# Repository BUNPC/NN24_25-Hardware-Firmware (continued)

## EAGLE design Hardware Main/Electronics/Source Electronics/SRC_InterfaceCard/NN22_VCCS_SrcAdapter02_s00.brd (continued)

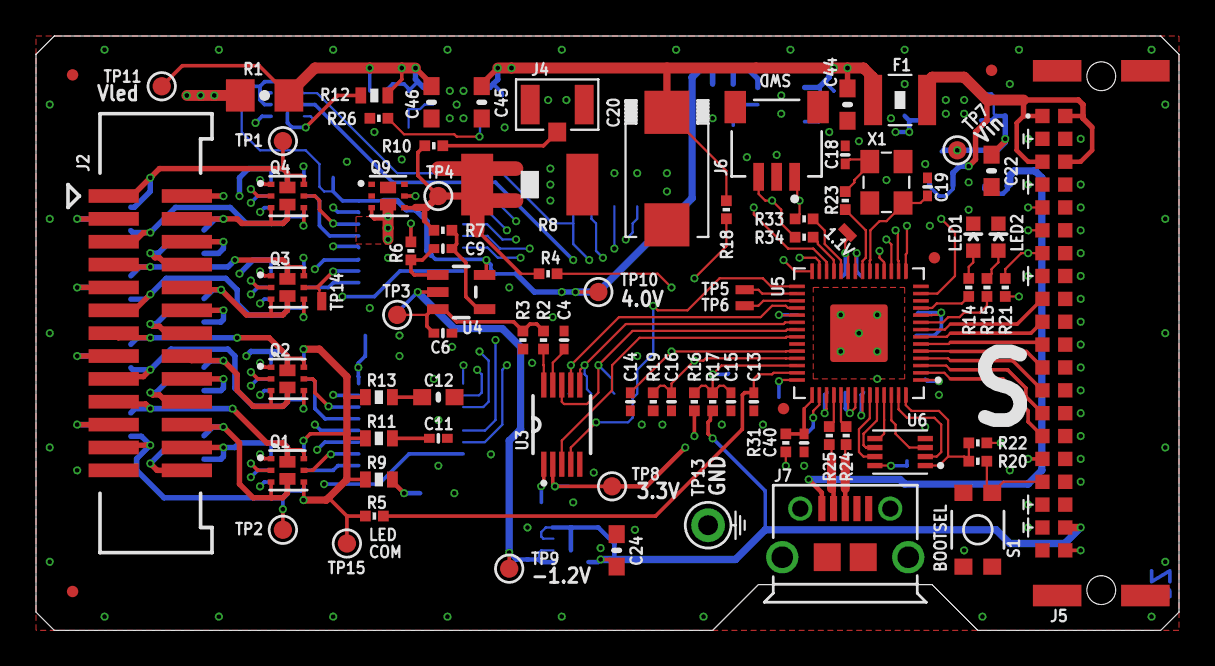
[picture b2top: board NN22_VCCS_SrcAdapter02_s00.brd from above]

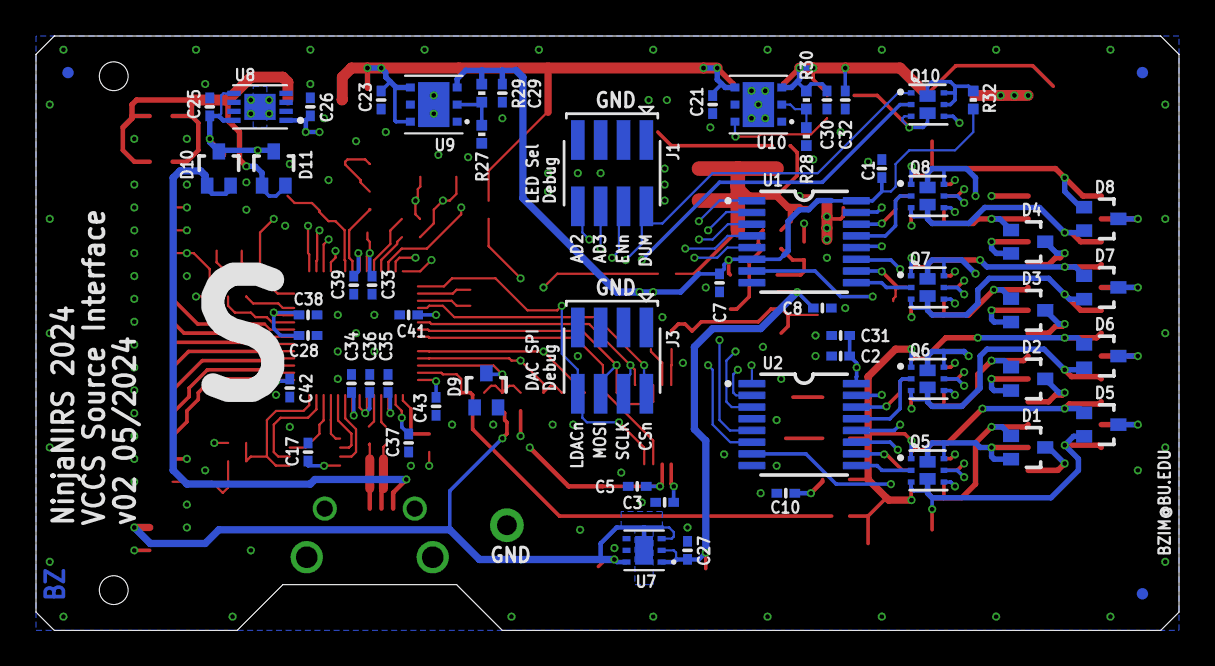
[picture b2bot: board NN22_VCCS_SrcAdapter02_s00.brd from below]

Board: 4 copper layers, 63.5 x 33.0 mm, 146 parts (60 on the bottom side), 109 nets.

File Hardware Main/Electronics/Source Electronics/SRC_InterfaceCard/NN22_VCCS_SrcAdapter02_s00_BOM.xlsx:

Designator | Value | Footprint | Populate | MPN | Manufacturer | MPN | Manufacturer
C1 | 0.1u | 0402-CAP | 1 | GRM155R71H104KE14D | Murata
C10 | 0.1u | 0402-CAP | 1 | GRM155R71H104KE14D | Murata
C11 | 10n | 0402-CAP | 1 | CL05B103KB5NNNC | Samsung
C12 | DNP | 0603-CAP | 0
C13 | 100p | 0402-CAP | 1 | CL05C101JB5NNNC | Samsung
C14 | 100p | 0402-CAP | 1 | CL05C101JB5NNNC | Samsung
C15 | 100p | 0402-CAP | 1 | CL05C101JB5NNNC | Samsung
C16 | 100p | 0402-CAP | 1 | CL05C101JB5NNNC | Samsung
C17 | 0.1u | 0402-CAP | 1 | GRM155R71H104KE14D | Murata
C18 | 27p | 0402-CAP | 1 | GCM1555C1H270JA16D | Murata
C19 | 27p | 0402-CAP | 1 | GCM1555C1H270JA16D | Murata
C2 | 0.1u | 0402-CAP | 1 | GRM155R71H104KE14D | Murata
C20 | 150u | 2917-CAP | 1 | TCJY157M016R0050E | KYOCERA AVX
C21 | 0.1u | 0402-CAP | 1 | GRM155R71H104KE14D | Murata
C22 | 10u | 0603-CAP | 1 | GRM188R6YA106MA73D | Murata
C23 | 0.1u | 0402-CAP | 1 | GRM155R71H104KE14D | Murata
C24 | 10u | 0603-CAP | 1 | GRM188R6YA106MA73D | Murata
C25 | 0.1u | 0402-CAP | 1 | GRM155R71H104KE14D | Murata
C26 | 4.7u | 0402-CAP | 1 | CL05A475MP5NRNC | Samsung
C27 | 4.7u | 0402-CAP | 1 | CL05A475MP5NRNC | Samsung
C28 | 4.7u | 0402-CAP | 1 | CL05A475MP5NRNC | Samsung
C29 | 4.7u | 0402-CAP | 1 | CL05A475MP5NRNC | Samsung
C3 | 0.1u | 0402-CAP | 1 | GRM155R71H104KE14D | Murata
C30 | 0.1u | 0402-CAP | 1 | GRM155R71H104KE14D | Murata
C31 | 4.7u | 0402-CAP | 1 | CL05A475MP5NRNC | Samsung
C32 | DNP | 0402-CAP | 0
C33 | 0.1u | 0402-CAP | 1 | GRM155R71H104KE14D | Murata
C34 | 0.1u | 0402-CAP | 1 | GRM155R71H104KE14D | Murata
C35 | 4.7u | 0402-CAP | 1 | CL05A475MP5NRNC | Samsung
C36 | 0.1u | 0402-CAP | 1 | GRM155R71H104KE14D | Murata
C37 | 4.7u | 0402-CAP | 1 | CL05A475MP5NRNC | Samsung
C38 | 0.1u | 0402-CAP | 1 | GRM155R71H104KE14D | Murata
C39 | 0.1u | 0402-CAP | 1 | GRM155R71H104KE14D | Murata
C4 | 10n | 0402-CAP | 1 | CL05B103KB5NNNC | Samsung
C40 | 4.7u | 0402-CAP | 1 | CL05A475MP5NRNC | Samsung
C41 | 0.1u | 0402-CAP | 1 | GRM155R71H104KE14D | Murata
C42 | 0.1u | 0402-CAP | 1 | GRM155R71H104KE14D | Murata
C43 | 0.1u | 0402-CAP | 1 | GRM155R71H104KE14D | Murata
C44 | 10u | 0603-CAP | 1 | GRM188R6YA106MA73D | Murata
C45 | 10u | 0603-CAP | 1 | GRM188R6YA106MA73D | Murata
C46 | 10u | 0603-CAP | 1 | GRM188R6YA106MA73D | Murata
C5 | 0.1u | 0402-CAP | 1 | GRM155R71H104KE14D | Murata
C6 | 100p | 0402-CAP | 1 | CL05C101JB5NNNC | Samsung
C7 | 0.1u | 0402-CAP | 1 | GRM155R71H104KE14D | Murata
C8 | 0.1u | 0402-CAP | 1 | GRM155R71H104KE14D | Murata
C9 | 100p | 0402-CAP | 1 | CL05C101JB5NNNC | Samsung
D1 | BAV70W | SOT323 | 1 | BAV70WT1G | onsemi
D10 | BAV70W | SOT323 | 1 | BAV70WT1G | onsemi
D11 | BAV70W | SOT323 | 1 | BAV70WT1G | onsemi
D2 | BAV70W | SOT323 | 1 | BAV70WT1G | onsemi
D3 | BAV70W | SOT323 | 1 | BAV70WT1G | onsemi
D4 | BAV70W | SOT323 | 1 | BAV70WT1G | onsemi
D5 | BAV70W | SOT323 | 1 | BAV70WT1G | onsemi
D6 | BAV70W | SOT323 | 1 | BAV70WT1G | onsemi
D7 | BAV70W | SOT323 | 1 | BAV70WT1G | onsemi
D8 | BAV70W | SOT323 | 1 | BAV70WT1G | onsemi
D9 | BAV70W | SOT323 | 1 | BAV70WT1G | onsemi
F1 | 0ZCH0035FF2G | 1210-FUSE | 1 | 0ZCH0035FF2G | Bel Fuse
FID1 | FIDUCIALUFIDUCIAL | MICRO-FIDUCIAL | 0
FID2 | FIDUCIALUFIDUCIAL | MICRO-FIDUCIAL | 0
FID3 | FIDUCIALUFIDUCIAL | MICRO-FIDUCIAL | 0
FID4 | FIDUCIALUFIDUCIAL | MICRO-FIDUCIAL | 0
FID5 | FIDUCIALUFIDUCIAL | MICRO-FIDUCIAL | 0
FID6 | FIDUCIALUFIDUCIAL | MICRO-FIDUCIAL | 0
FID7 | FIDUCIALUFIDUCIAL | MICRO-FIDUCIAL | 0
FID8 | FIDUCIALUFIDUCIAL | MICRO-FIDUCIAL | 0
J1 | M04X2_0.050_SMD_NO_CREAM | M04X2_0.050_SMD_NO_CREAM | 0
J2 | M13X2_0.050_SHF | M13X2_0.050_SHF | 1 | 3220-26-0300-00 | CNC Tech | 3220-26-0300-00-TR | CNC Tech
J3 | M04X2_0.050_SMD_NO_CREAM | M04X2_0.050_SMD_NO_CREAM | 0
J4 | U.FL | U.FL | 1 | 1909763-1 | TE Connectivity
J5 | M20X2_HARFLEX_M | M20X2_HARFLEX_M | 1 | 15150402601000 | HARTING Elektronik
J6 | M03X1_JST_SH_RA | M03X1_JST_SH_SM_RA | 1 | SM03B-SRSS-TB | JST
J7 | USB-MICRO | USB-MICRO | 1 | 10118194-0001LF | Amphenol Communications Solutions
LED1 |  | LED-0603 | 1 | LTST-C191KRKT | Lite-On
LED2 |  | LED-0603 | 1 | LTST-C191KGKT | Lite-On
Q1 | MOSFET-DUAL-N-UDFN8 | UDFN8 | 1 | SSM6N67NU,LF | Toshiba
Q10 | MOSFET-DUAL-N-UDFN8 | UDFN8 | 1 | SSM6N67NU,LF | Toshiba
Q2 | MOSFET-DUAL-N-UDFN8 | UDFN8 | 1 | SSM6N67NU,LF | Toshiba
Q3 | MOSFET-DUAL-N-UDFN8 | UDFN8 | 1 | SSM6N67NU,LF | Toshiba
Q4 | MOSFET-DUAL-N-UDFN8 | UDFN8 | 1 | SSM6N67NU,LF | Toshiba
Q5 | MOSFET-DUAL-N-UDFN8 | UDFN8 | 1 | SSM6N67NU,LF | Toshiba
Q6 | MOSFET-DUAL-N-UDFN8 | UDFN8 | 1 | SSM6N67NU,LF | Toshiba
Q7 | MOSFET-DUAL-N-UDFN8 | UDFN8 | 1 | SSM6N67NU,LF | Toshiba
Q8 | MOSFET-DUAL-N-UDFN8 | UDFN8 | 1 | SSM6N67NU,LF | Toshiba
Q9 | MOSFET-DUAL-N-UDFN8 | UDFN8 | 1 | SSM6N67NU,LF | Toshiba
R1 | 0 | 1206 | 1 | RC1206JR-070RL | Yageo
R10 | 100 | 0402-RES | 1 | RC0402FR-07100RL | Yageo
R11 | 1 | 0603-RES | 1 | RC0603FR-071RL | Yageo
R12 | 150 | 0603-RES | 1 | RC0603FR-07150RL | Yageo
R13 | DNP | 0603-RES | 0
R14 | 1.2k | 0402-RES | 1 | RC0402FR-071K2L | Yageo
R15 | 1.2k | 0402-RES | 1 | RC0402FR-071K2L | Yageo
R16 | 10k | 0402-RES | 1 | RC0402FR-1310KL | Yageo
R17 | 28k | 0402-RES | 1 | RC0402FR-0728KL | Yageo
R18 | 28k | 0402-RES | 1 | RC0402FR-0728KL | Yageo
R19 | 10k | 0402-RES | 1 | RC0402FR-1310KL | Yageo
R2 | 10k | 0402-RES | 1 | RC0402FR-1310KL | Yageo
R20 | 1.2k | 0402-RES | 1 | RC0402FR-071K2L | Yageo
R21 | 100k | 0402-RES | 1 | RC0402FR-07100KL | Yageo
R22 | 100k | 0402-RES | 1 | RC0402FR-07100KL | Yageo
R23 | 1.2k | 0402-RES | 1 | RC0402FR-071K2L | Yageo
R24 | 27 | 0402-RES | 1 | RC0402FR-0727RL | Yageo
R25 | 27 | 0402-RES | 1 | RC0402FR-0727RL | Yageo
R26 | 100k | 0402-RES | 1 | RC0402FR-07100KL | Yageo
R27 | 10k | 0402-RES | 1 | RC0402FR-1310KL | Yageo
R28 | 10k | 0402-RES | 1 | RC0402FR-1310KL | Yageo
R29 | 24k | 0402-RES | 1 | RC0402FR-0724KL | Yageo
R3 | 24k | 0402-RES | 1 | RC0402FR-0724KL | Yageo
R30 | 28k | 0402-RES | 1 | RC0402FR-0728KL | Yageo
R31 | 27 | 0402-RES | 1 | RC0402FR-0727RL | Yageo
R32 | 10k | 0402-RES | 1 | RC0402FR-1310KL | Yageo
R33 | 27 | 0402-RES | 1 | RC0402FR-0727RL | Yageo
R34 | 27 | 0402-RES | 1 | RC0402FR-0727RL | Yageo
R4 | 10k | 0402-RES | 1 | RC0402FR-1310KL | Yageo
R5 | 10k | 0402-RES | 1 | RC0402FR-1310KL | Yageo
R6 | 100 | 0402-RES | 1 | RC0402FR-07100RL | Yageo
R7 | 1.2k | 0402-RES | 1 | RC0402FR-071K2L | Yageo
R8 | 8.2 | R2512 | 1 | ERJ1TRQJ8R2U | Panasonic
R9 | 10 | 0603-RES | 1 | RC0603FR-0710RL | Yageo
S1 | SWITCH-MOMENTARY-2SMD-3 | TACTILE_SWITCH_SMD-3 | 1 | KMR231NGLFS | C&K Components
TP1 | TESTPOINT_ROUND | TESTPAD_ROUND | 0
TP10 | TESTPOINT_ROUND | TESTPAD_ROUND | 0
TP11 | TESTPOINT_ROUND | TESTPAD_ROUND | 0
TP12 | TESTPOINTPADSMALL | TESTPAD_SMALL | 0
TP13 | TESTPOINT1X01 | 1X01 | 0
TP14 | TESTPOINTPADSMALL | TESTPAD_SMALL | 0
TP15 | TESTPOINT_ROUND | TESTPAD_ROUND | 0
TP2 | TESTPOINT_ROUND | TESTPAD_ROUND | 0
TP3 | TESTPOINT_ROUND | TESTPAD_ROUND | 0
TP4 | TESTPOINT_ROUND | TESTPAD_ROUND | 0
TP5 | TESTPOINTPADSMALL | TESTPAD_SMALL | 0
TP6 | TESTPOINTPADSMALL | TESTPAD_SMALL | 0
TP7 | TESTPOINT_ROUND | TESTPAD_ROUND | 0
TP8 | TESTPOINT_ROUND | TESTPAD_ROUND | 0
TP9 | TESTPOINT_ROUND | TESTPAD_ROUND | 0
U1 | 74HC238_TSSOP | TSSOP16 | 1 | SN74HCS238PWR | Texas Instruments
U10 | LDL212_DFN6_3X3 | DFN6_3X3MM | 1 | LDL212PUR | STMicroelectronics
U2 | 74HC238_TSSOP | TSSOP16 | 1 | SN74HCS238PWR | Texas Instruments
U3 | AD5683R_MSOP | MSOP10 | 1 | AD5683RARMZ | Analog Devices
U4 | OPA392_SOT23 | SOT23-5 | 1 | OPA392DBVR | Texas Instruments
U5 | RP2040 | QFN-56_EP | 1 | SC0914(7) | Raspberry Pi
U6 | W25Q_USON | USON8L-2X3MM | 1 | W25Q16JVUXIQ TR | Winbond
U7 | ADP7182_WSON | WSON6 | 1 | ADP7182ACPZN-R7 | Analog Devices
U8 | MCP1755_DFN | DFN8_2X3MM | 1 | MCP1755-3302E/MC | Microchip
U9 | LDL212_DFN6_3X3 | DFN6_3X3MM | 1 | LDL212PUR | STMicroelectronics
X1 | CRYSTAL-3.2-2.5 | CRYSTAL-3.2-2.5 | 1 | 403I35D12M00000 | CTS Components

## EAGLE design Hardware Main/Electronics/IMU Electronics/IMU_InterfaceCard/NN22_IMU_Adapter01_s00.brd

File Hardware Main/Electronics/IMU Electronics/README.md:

# IMU Electronics

All IMU electronics files are located in this folder. 

There is not a dedicated IMU backboard part as the IMU interface cards are intended to be used with the existing detector backplanes in place of a detector interface card.

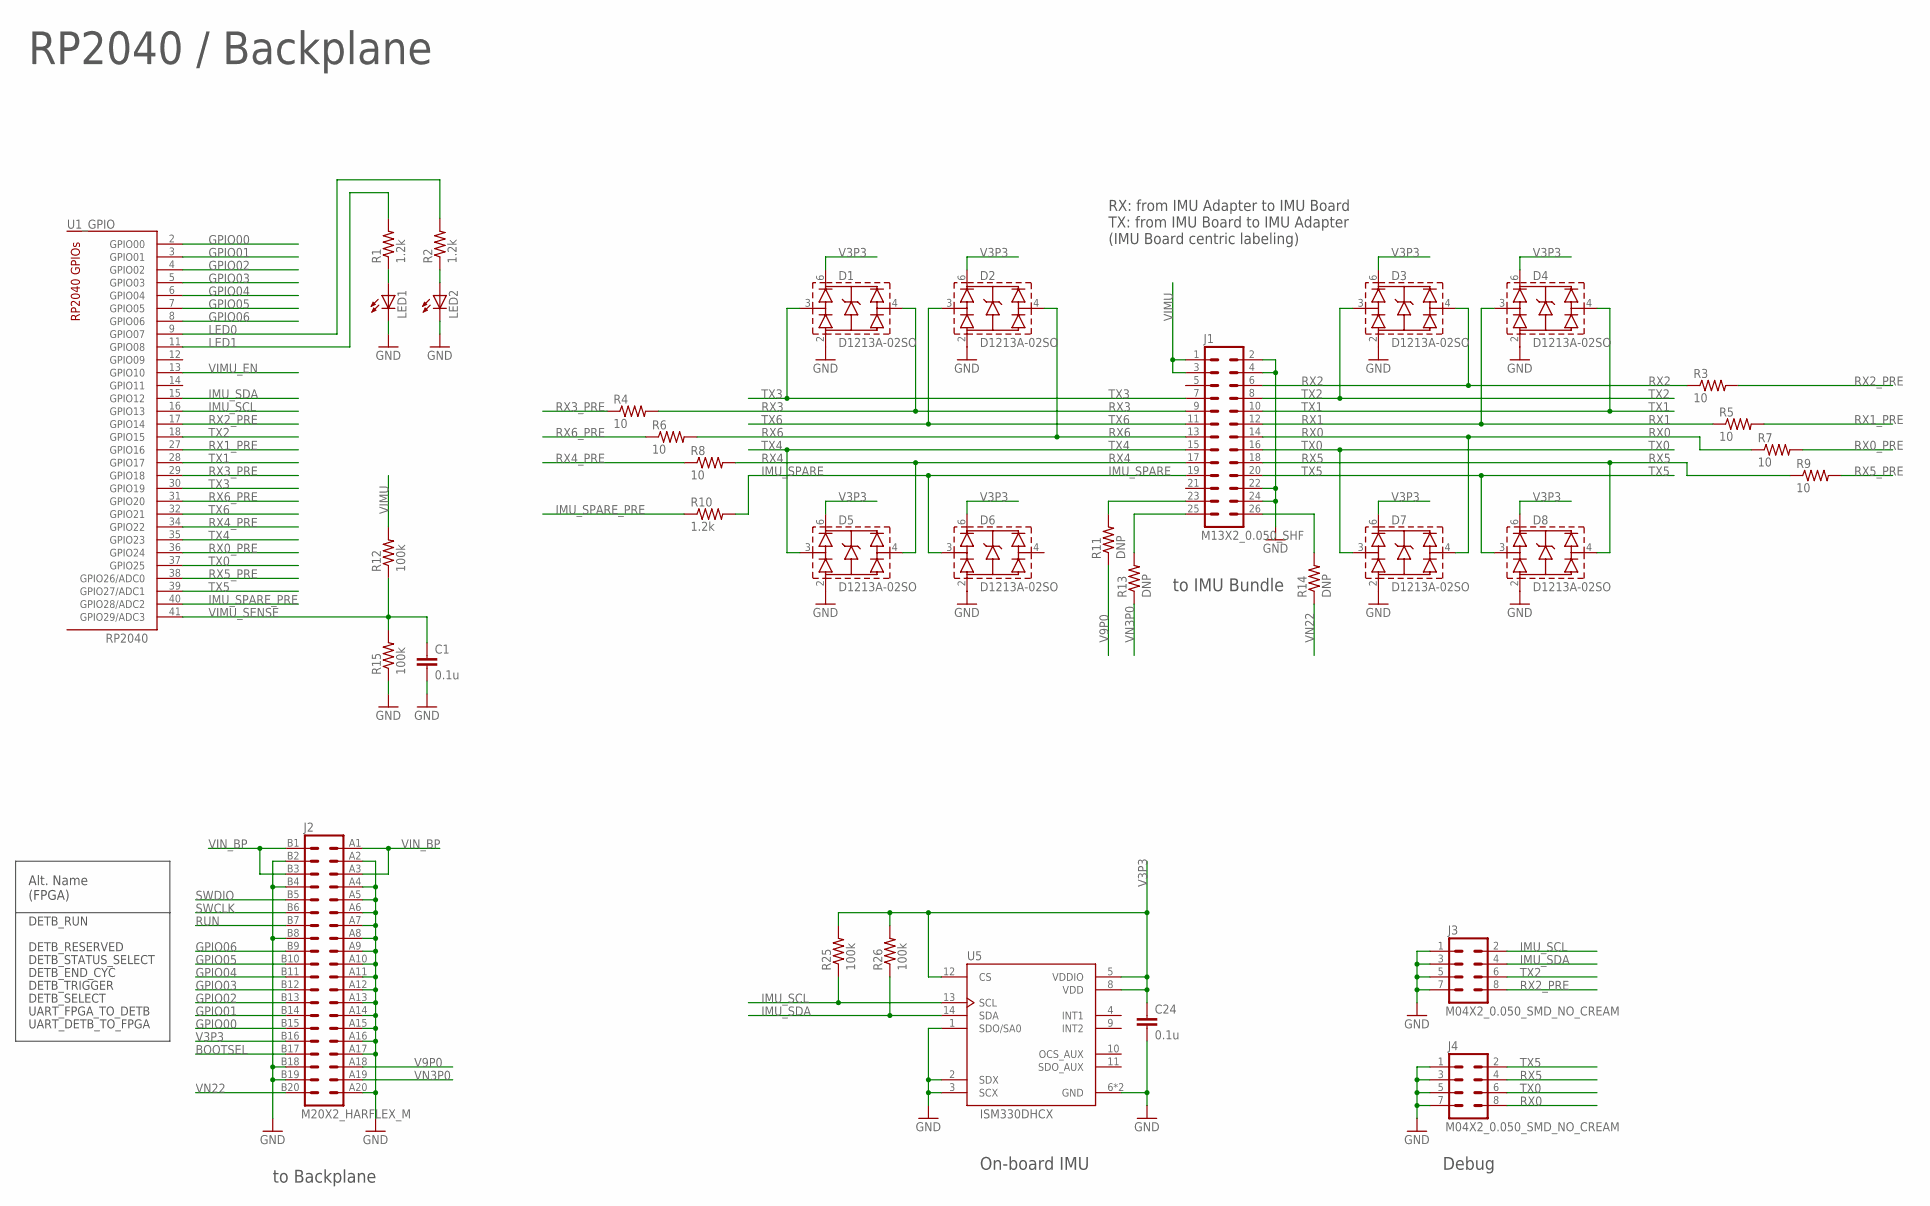
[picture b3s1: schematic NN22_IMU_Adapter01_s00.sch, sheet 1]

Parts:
C1, C24: 0.1u; 0402-CAP
D1, D2, D3, D4, D5, D6, D7, D8: D1213A-02SO; SOT23-6
J1: M13X2_0.050_SHF
J2: M20X2_HARFLEX_M
J3, J4: M04X2_0.050_SMD_NO_CREAM
LED1, LED2: LED0603; LED-0603
R1, R2, R10: 1.2k; 0402-RES
R3, R4, R5, R6, R7, R8, R9: 10; 0402-RES
R11, R13, R14: DNP; 0603-RES
R12, R15, R25, R26: 100k; 0402-RES
U1: RP2040; QFN-56_EP
U5: ISM330DHCX; LGA14-L

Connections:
BOOTSEL: J2.B17 (33); also elsewhere on the board
GND: C1.2, C24.2, D1.2 (VN), D2.2 (VN), D3.2 (VN), D4.2 (VN), D5.2 (VN), D6.2 (VN), D7.2 (VN), D8.2 (VN), J1.2, J1.4, J1.22, J1.24, J2.A2 (4), J2.A4 (8), J2.A5 (10), J2.A6 (12), J2.A7 (14), J2.A8 (16), J2.A9 (18), J2.A10 (20), J2.A11 (22), J2.A12 (24), J2.A13 (26), J2.A14 (28), J2.A15 (30), J2.A16 (32), J2.A17 (34), J2.A20 (40), J2.B2 (3), J2.B4 (7), J2.B8 (15), J2.B18 (35), J2.B19 (37), J3.1, J3.3, J3.5, J3.7, J4.1, J4.3, J4.5, J4.7, LED1.C, LED2.C, R15.1, U5.1 (SDO/SA0), U5.2 (SDX), U5.3 (SCX), U5.6 (GND), U5.7 (GND); also elsewhere on the board
GPIO00: J2.B15 (29), U1.2 (GPIO00)
GPIO01: J2.B14 (27), U1.3 (GPIO01)
GPIO02: J2.B13 (25), U1.4 (GPIO02)
GPIO03: J2.B12 (23), U1.5 (GPIO03)
GPIO04: J2.B11 (21), U1.6 (GPIO04)
GPIO05: J2.B10 (19), U1.7 (GPIO05)
GPIO06: J2.B9 (17), U1.8 (GPIO06)
IMU_SCL: J3.2, R25.1, U1.16 (GPIO13), U5.13 (SCL)
IMU_SDA: J3.4, R26.1, U1.15 (GPIO12), U5.14 (SDA)
IMU_SPARE: D6.3 (CH1), J1.19, R10.2
IMU_SPARE_PRE: R10.1, U1.40 (GPIO28/ADC2)
LED0: R2.2, U1.9 (GPIO07)
LED1: R1.2, U1.11 (GPIO08)
unnamed: J1.23, R11.2
unnamed: J1.25, R13.2
unnamed: J1.26, R14.2
unnamed: LED1.A, R1.1
unnamed: LED2.A, R2.1
RUN: J2.B7 (13); also elsewhere on the board
RX0: D7.4 (CH2), J1.14, J4.8, R7.1
RX0_PRE: R7.2, U1.36 (GPIO24)
RX1: D4.3 (CH1), J1.12, R5.1
RX1_PRE: R5.2, U1.27 (GPIO16)
RX2: D3.4 (CH2), J1.6, R3.1
RX2_PRE: J3.8, R3.2, U1.17 (GPIO14)
RX3: D1.4 (CH2), J1.9, R4.2
RX3_PRE: R4.1, U1.29 (GPIO18)
RX4: D5.4 (CH2), J1.17, R8.2
RX4_PRE: R8.1, U1.34 (GPIO22)
RX5: D8.4 (CH2), J1.18, J4.4, R9.1
RX5_PRE: R9.2, U1.38 (GPIO26/ADC0)
RX6: D2.4 (CH2), J1.13, R6.2
RX6_PRE: R6.1, U1.31 (GPIO20)
SWCLK: J2.B6 (11); also elsewhere on the board
SWDIO: J2.B5 (9); also elsewhere on the board
TX0: D7.3 (CH1), J1.16, J4.6, U1.37 (GPIO25)
TX1: D4.4 (CH2), J1.10, U1.28 (GPIO17)
TX2: D3.3 (CH1), J1.8, J3.6, U1.18 (GPIO15)
TX3: D1.3 (CH1), J1.7, U1.30 (GPIO19)
TX4: D5.3 (CH1), J1.15, U1.35 (GPIO23)
TX5: D8.3 (CH1), J1.20, J4.2, U1.39 (GPIO27/ADC1)
TX6: D2.3 (CH1), J1.11, U1.32 (GPIO21)
V3P3: C24.1, D1.6 (VP), D2.6 (VP), D3.6 (VP), D4.6 (VP), D5.6 (VP), D6.6 (VP), D7.6 (VP), D8.6 (VP), J2.B16 (31), R25.2, R26.2, U5.5 (VDDIO), U5.8 (VDD), U5.12 (CS); also elsewhere on the board
V9P0: J2.A18 (36), R11.1
VIMU: J1.1, J1.3, R12.2; also elsewhere on the board
VIMU_EN: U1.13 (GPIO10); also elsewhere on the board
VIMU_SENSE: C1.1, R12.1, R15.2, U1.41 (GPIO29/ADC3)
VIN_BP: J2.A1 (2), J2.A3 (6), J2.B1 (1), J2.B3 (5); also elsewhere on the board
VN3P0: J2.A19 (38), R13.1
VN22: J2.B20 (39), R14.1

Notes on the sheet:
RP2040 / Backplane
to Backplane
UART_DETB_TO_FPGA
UART_FPGA_TO_DETB
DETB_SELECT
DETB_TRIGGER
DETB_END_CYC
DETB_STATUS_SELECT
DETB_RESERVED
DETB_RUN
Alt. Name (FPGA)
to IMU Bundle
Debug
RX: from IMU Adapter to IMU Board TX: from IMU Board to IMU Adapter (IMU Board centric labeling)
On-board IMU

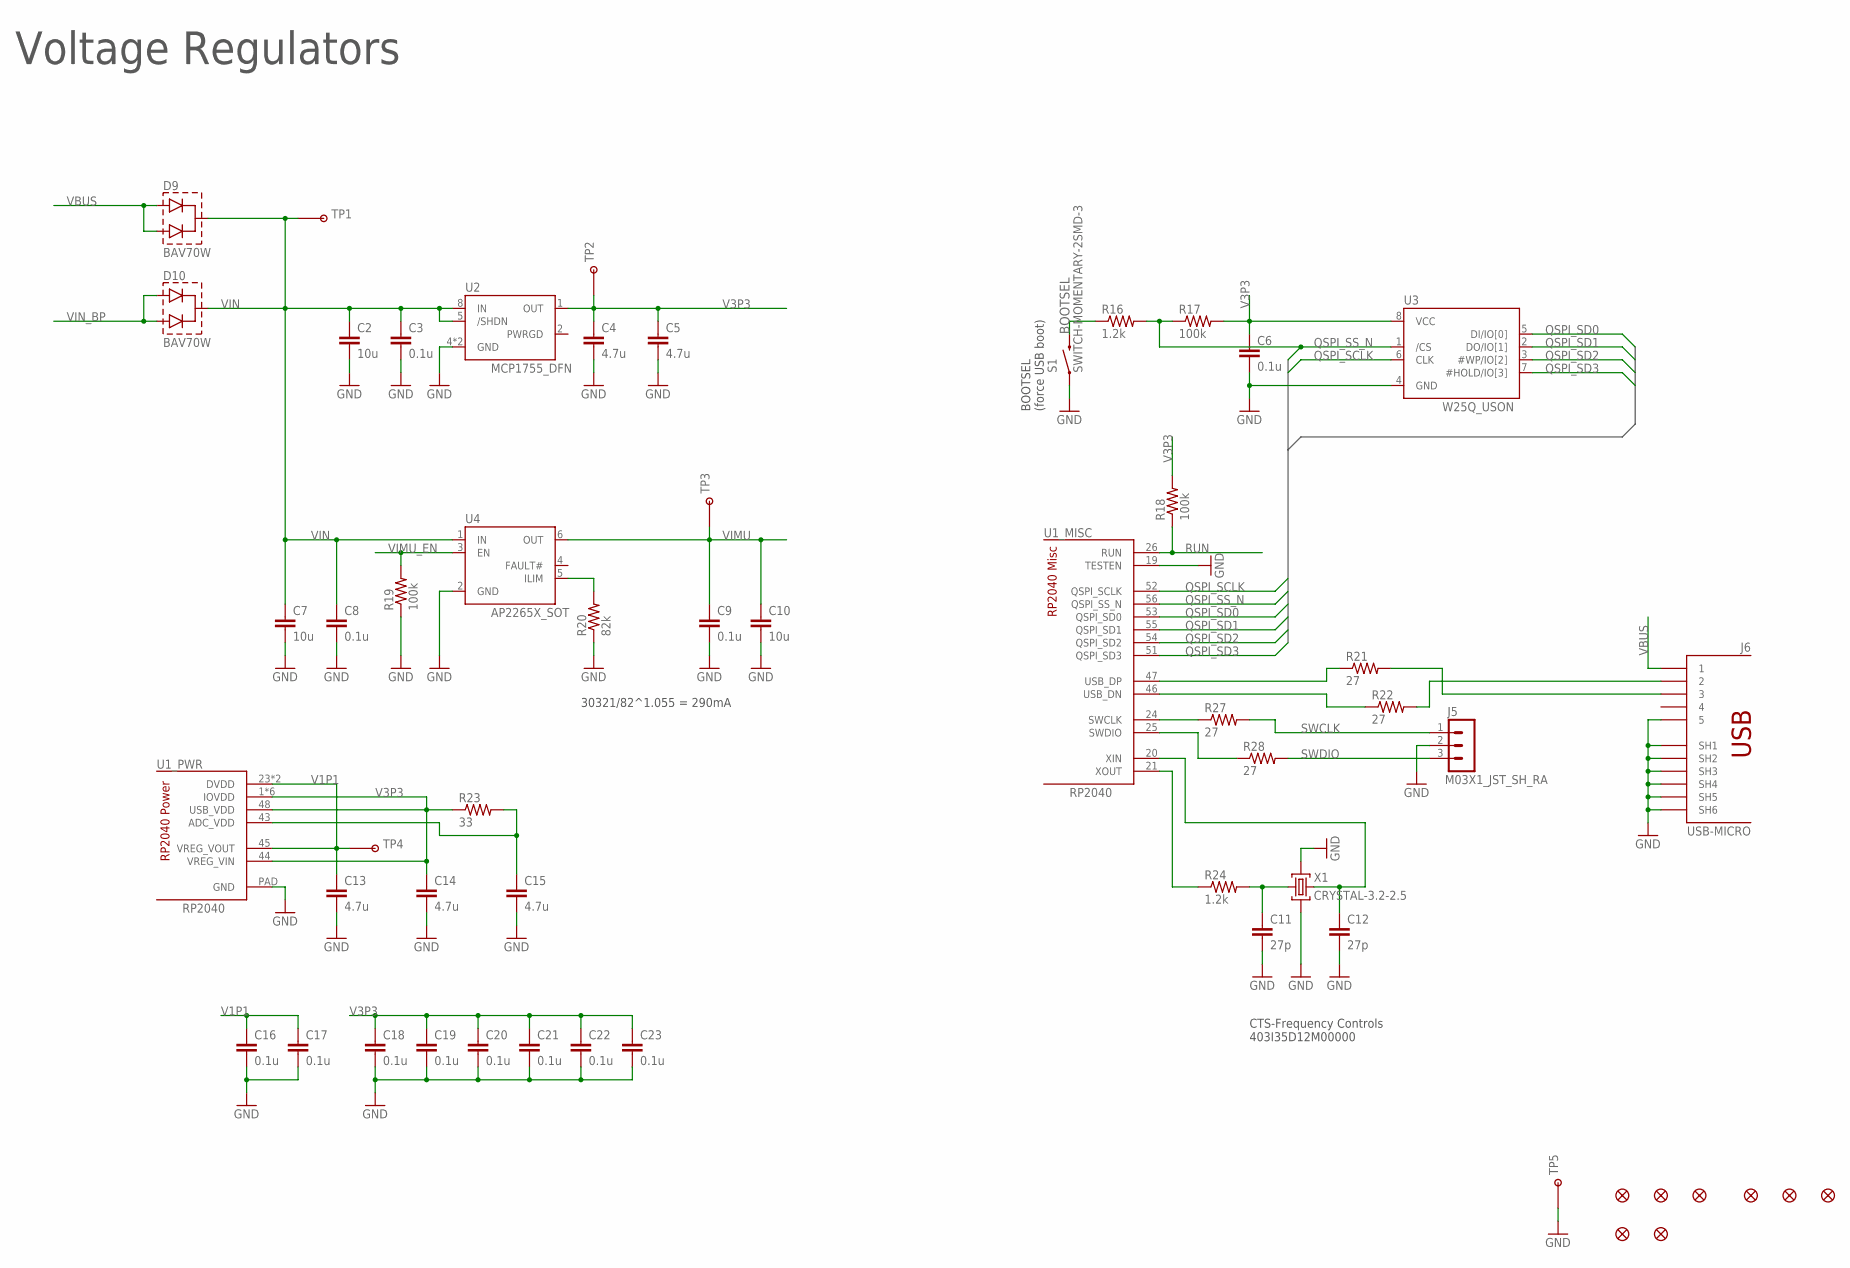
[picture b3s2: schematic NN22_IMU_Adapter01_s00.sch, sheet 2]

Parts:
C2, C7, C10: 10u; 0603-CAP
C3, C6, C8, C9, C16, C17, C18, C19, C20, C21, C22, C23: 0.1u; 0402-CAP
C4, C5, C13, C14, C15: 4.7u; 0402-CAP
C11, C12: 27p; 0402-CAP
D9, D10: BAV70W; SOT323
FID1, FID2, FID3, FID4, FID5, FID6, FID7, FID8: FIDUCIALUFIDUCIAL; MICRO-FIDUCIAL
J5: M03X1_JST_SH_RA; M03X1_JST_SH_SM_RA
J6: USB-MICRO
R16, R24: 1.2k; 0402-RES
R17, R18, R19: 100k; 0402-RES
R20: 82k; 0402-RES
R21, R22, R27, R28: 27; 0402-RES
R23: 33; 0402-RES
S1: SWITCH-MOMENTARY-2SMD-3; TACTILE_SWITCH_SMD-3
TP1, TP2, TP3: TESTPOINT_ROUND; TESTPAD_ROUND
TP4: TESTPOINTPADSMALL; TESTPAD_SMALL
TP5: TESTPOINT1X01; 1X01
U1: RP2040; QFN-56_EP
U2: MCP1755_DFN; DFN8_2X3MM
U3: W25Q_USON; USON8L-2X3MM
U4: AP2265X_SOT; SOT23-6
X1: CRYSTAL-3.2-2.5

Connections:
BOOTSEL: R16.1, S1.4 (2); also elsewhere on the board
GND: C2.2, C3.2, C4.2, C5.2, C6.2, C7.2, C8.2, C9.2, C10.2, C11.2, C12.2, C13.2, C14.2, C15.2, C16.2, C17.2, C18.2, C19.2, C20.2, C21.2, C22.2, C23.2, J5.2, J6.5, J6.SH1, J6.SH2, J6.SH3, J6.SH4, J6.SH5, J6.SH6, R19.1, R20.1, S1.1, TP5.1, U1.19 (TESTEN), U1.PAD (GND), U2.4 (GND), U2.P (GND), U3.4 (GND), U4.2 (GND), X1.2 (GND), X1.4 (GND); also elsewhere on the board
unnamed: R20.2, U4.5 (ILIM)
unnamed: C12.1, U1.20 (XIN), X1.3 (C2)
unnamed: C11.1, R24.2, X1.1 (C1)
unnamed: R24.1, U1.21 (XOUT)
unnamed: R21.1, U1.47 (USB_DP)
unnamed: R22.1, U1.46 (USB_DN)
unnamed: J6.2, R22.2
unnamed: J6.3, R21.2
unnamed: C15.1, R23.2, U1.43 (ADC_VDD)
QSPI_SCLK: U1.52 (QSPI_SCLK), U3.6 (CLK)
QSPI_SD0: U1.53 (QSPI_SD0), U3.5 (DI/IO[0])
QSPI_SD1: U1.55 (QSPI_SD1), U3.2 (DO/IO[1])
QSPI_SD2: U1.54 (QSPI_SD2), U3.3 (#WP/IO[2])
QSPI_SD3: U1.51 (QSPI_SD3), U3.7 (#HOLD/IO[3])
QSPI_SS_N: R16.2, R17.1, U1.56 (QSPI_SS_N), U3.1 (/CS)
RUN: R18.1, U1.26 (RUN); also elsewhere on the board
SWCLK: J5.1, R27.2; also elsewhere on the board
SWCLK_PRE: R27.1, U1.24 (SWCLK)
SWDIO: J5.3, R28.2; also elsewhere on the board
SWDIO_PRE: R28.1, U1.25 (SWDIO)
V1P1: C13.1, C16.1, C17.1, TP4.P$1, U1.23 (DVDD), U1.45 (VREG_VOUT), U1.50 (DVDD)
V3P3: C4.1, C5.1, C6.1, C14.1, C18.1, C19.1, C20.1, C21.1, C22.1, C23.1, R17.2, R18.2, R23.1, TP2.P$1, U1.1 (IOVDD), U1.10 (IOVDD), U1.22 (IOVDD), U1.33 (IOVDD), U1.42 (IOVDD), U1.44 (VREG_VIN), U1.48 (USB_VDD), U1.49 (IOVDD), U2.1 (OUT), U3.8 (VCC); also elsewhere on the board
VBUS: D9.1 (A1), D9.2 (A2), J6.1
VIMU: C9.1, C10.1, TP3.P$1, U4.6 (OUT); also elsewhere on the board
VIMU_EN: R19.2, U4.3 (EN); also elsewhere on the board
VIN: C2.1, C3.1, C7.1, C8.1, D9.3 (C), D10.3 (C), TP1.P$1, U2.5 (/SHDN), U2.8 (IN), U4.1 (IN)
VIN_BP: D10.1 (A1), D10.2 (A2); also elsewhere on the board

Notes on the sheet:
Voltage Regulators
BOOTSEL (force USB boot)
CTS-Frequency Controls 403I35D12M00000
30321/82^1.055 = 290mA

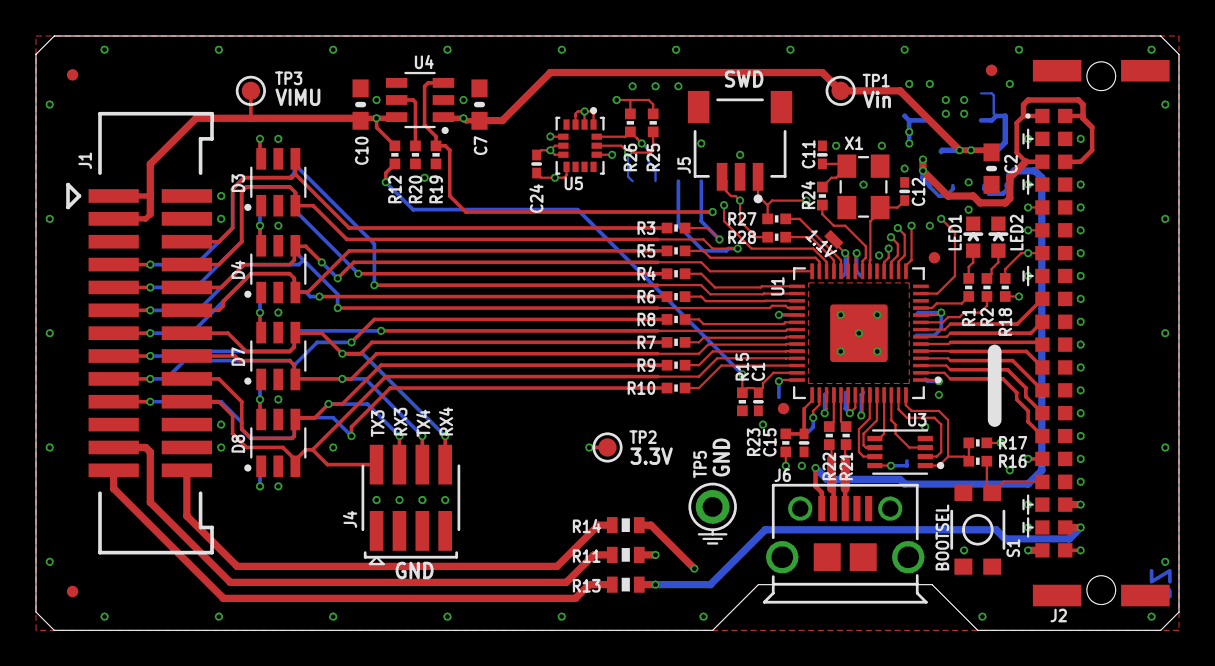
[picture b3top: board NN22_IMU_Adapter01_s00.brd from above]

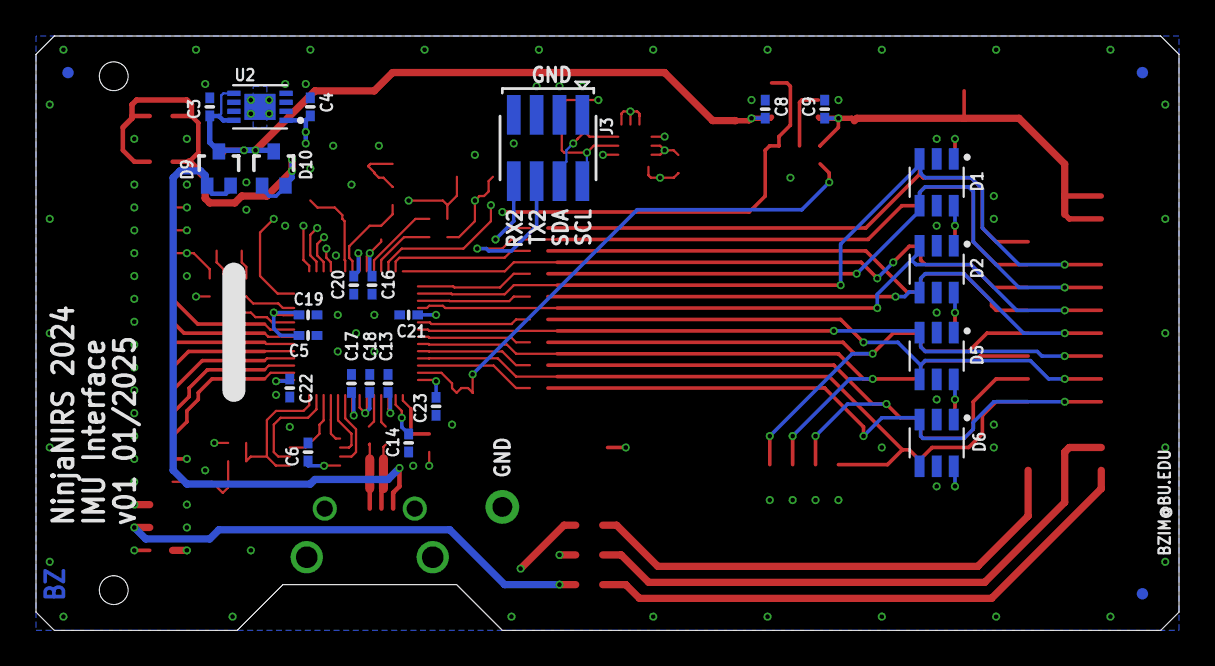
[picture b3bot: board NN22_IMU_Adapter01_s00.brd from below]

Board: 4 copper layers, 63.5 x 33.0 mm, 90 parts (27 on the bottom side), 72 nets.

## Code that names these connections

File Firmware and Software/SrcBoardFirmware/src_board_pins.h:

// ---  NinjaNIRS 2024  ---
// Pin constants for NN22_VCCS_SrcAdapter02_s00 board
//
// Initial version: 2024-03-26
// Bernhard Zimmermann - bzim@bu.edu
// Boston University Neurophotonics Center
//

// Backplane pins: GPIO00 - GPIO06
const uint UART_TX_PIN = 0;
const uint UART_RX_PIN = 1;
const uint BOARD_SELECTN_PIN = 2;
//const uint STEP_PIN = 3; // defined in led_sel_fsm.pio
const uint LED_EN_IN_PIN = 4;
const uint STATUS_SELECT_PIN = 5;
const uint RESERVED_PIN = 6;

// Misc Pins
const uint LED_R_PIN = 8;
const uint LED_G_PIN = 7;
const uint SPARE_PINS[] = {19, 20};

// DAC pins
const uint CSN_DAC_PIN = 21;
const uint SCLK_DAC_PIN = 22;
const uint MOSI_DAC_PIN = 23;
const uint RESETN_DAC_PIN = 24;
const uint LDACN_DAC_PIN = 18;

// LED (Source optode) control pins
const uint VLED_EN_PIN = 10;
const uint LED_AD_PINS[] = {12, 13, 14, 15};
const uint LED_ENN_PIN = 16;
const uint DUMMY_EN_PIN = 17;
 
// Analog sense pins
const uint LED_CURR_SENSE_PIN = 26;
const uint LED_CURR_SENSE_ACH = 0;
const uint VIN_SENSE_PIN = 27;
const uint VIN_SENSE_ACH = 1;
const uint VNEG_SENSE_PIN = 28;
const uint VNEG_SENSE_ACH = 2;
const uint LED_COM_SENSE_PIN = 29;
const uint LED_COM_SENSE_ACH = 3;
const uint TEMP_SENSE_ACH = 4;

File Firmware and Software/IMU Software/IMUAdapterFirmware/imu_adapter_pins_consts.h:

// ---  NinjaNIRS 2025  ---
// Pin constants for NN22_IMU_Adapter01_s00 board
//
// Initial version: 2024-04-10
// Bernhard Zimmermann - bzim@bu.edu
// Boston University Neurophotonics Center
//


// Backplane pins: GPIO00 - GPIO06
const uint UART_TX_PIN = 0;
const uint UART_RX_PIN = 1;
const uint BOARD_SELECT_PIN = 2;
//const uint TRG_PIN = 3; // check also adcacq.pio
const uint END_CYC_PIN = 4;
const uint STATUS_SELECT_PIN = 5;
const uint RESERVED_PIN = 6;

// Misc Pins
const uint VIMU_EN_PIN = 10;
const uint LED_R_PIN = 8;
const uint LED_G_PIN = 7;
const uint VIMU_SENSE_PIN = 29;
const uint VIMU_SENSE_ACH = 3;

const uint TEMP_SENSE_ACH = 4;

// IMU pins
// RX: from IMU Adapter to IMU Board
// TX: from IMU Board to IMU Adapter
// (IMU Board centric labeling)
#define N_EXT_IMUS 7
const uint IMU_TX_PINS[] = {25, 17, 15, 19, 23, 27, 20};//{19, 21, 23, 27, 25, 15, 17, 13};
const uint IMU_RX_PINS[] = {24, 16, 14, 18, 22, 26, 21};//{18, 20, 22, 26, 24, 14, 16, 12};

const uint INT_IMU_SDA_PIN = 12;
const uint INT_IMU_SCL_PIN = 13;
#define INT_ACC_I2C i2c1

// IMU constants

// scaling factors and offsets
// const float ACC_ACCEL_SCF = 4.0/(2<<14);
// const float ACC_GYRO_SCF = 250.0/(2<<14);
// const float ACC_TEMP_SCF = 1.0/256;
// const float ACC_TEMP_OFFSET = 25.0;


const uint IMU_BAUD_RATE = 250000;
const uint N_BYTES_PER_IMU = 17;
#define N_WORDS_PER_IMU 9

// Address of ISM330DHCX 6DOF IMU
// 0x6A if SA0 = low, 0x6B if SA0 = high
// (SA0 pin on sparkfun board is pulled high by default)
const uint8_t ACC_ADDR= 0x6A;
const uint8_t ACC_WHO_AM_I_ADDR = 0x0F;
const uint8_t ACC_WHO_AM_I_VAL = 0x6B;
const uint8_t ACC_CTRL3_C_ADDR = 0x12; 
const uint8_t ACC_CTRL3_C_VAL = 0x03; // software reset
const uint8_t ACC_CTRL1_XL_ADDR = 0x10;
const uint8_t ACC_CTRL1_XL_VAL = 0b01111000; //accel ODR (833Hz) and FS (+-4g)
const uint8_t ACC_CTRL2_G_VAL = 0b01110000; //gyro ODR (833Hz) and FS (+-250dps)
const uint8_t ACC_OUT_TEMP_L_ADDR = 0x20; //start of output registers
const uint8_t ACC_CTRL5_C_ADDR = 0x14;

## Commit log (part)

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2025-06-23 Uploaded ninjaCasing and Setup Guide
    ninjaCasing uploaded with revised folder structure along with updated setup guide that links to the new repository
2025-10-18 Create CombinedBackplane01_BOM.txt
    Add backplane BOM
2025-10-18 Add source interface card BOM.
